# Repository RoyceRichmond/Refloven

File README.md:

# Refloven

this projects aims to be a low cost and customisable reflow oven board, i inspired this in the job made by @rocketscream reflow oven shield with some additional hardware so it can have more I/O pins avaliable and also usb so there's need of external programmer.

currently working to fix some problems, v2 is actually really stable and works fine. have fun and as a side note, use the v1 to make the v2 got it ? (like a 3d printer )

v1 is the easies one to build, all by hand and some extra wire.

v2 is a little more complicated to, but if you sucessfully assembled v1 and tested it you have everything on your side. it works either with 328p or 328pb only difference is how to program it and the mapping of the i/o

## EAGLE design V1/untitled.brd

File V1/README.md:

side note, you must change the i/o pins assigned to the 595 'cause a6 and a7 are just analog and not digital (why i dont undestand but meh) otherwise te lcd wont work

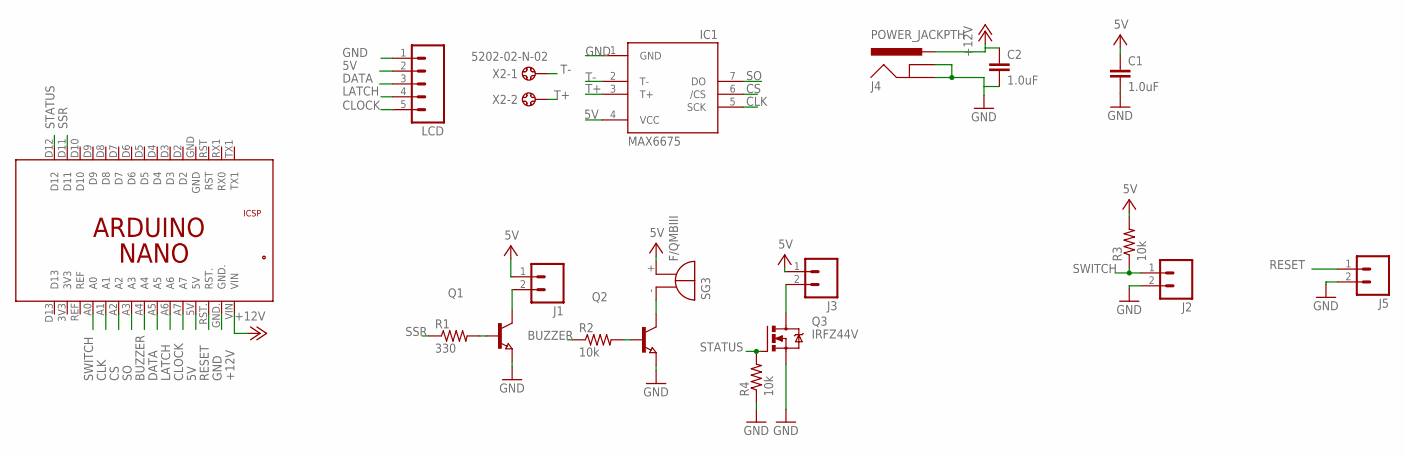
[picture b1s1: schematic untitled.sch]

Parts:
C1, C2: 1.0uF; 1206-CAP
IC1: MAX6675; SO08
J1, J2, J3, J5: M02PTH; 1X02
J4: POWER_JACKPTH; POWER_JACK_PTH
LCD: M05PTH; 1X05
PCB2: ARDUINO_NANO_RHEYD; ARDUINO_NANO
Q1, Q2: NPN-TRANSISTOR_SOT23; SOT23
Q3: IRFZ44V; TO220BH
R1: 330; R1206
R2, R3, R4: 10k; R1206
SG3: F/QMBIII
X2: 5202-02-N-02

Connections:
5V: C1.1, IC1.4 (VCC), J1.1, J3.1, LCD.2, PCB2.5V, R3.2, SG3.+ (-)
+12V: C2.1, J4.PWR, PCB2.VIN
BUZZER: PCB2.A4, R2.1
CLK: IC1.5 (SCK), PCB2.A1
CLOCK: LCD.5, PCB2.A7
CS: IC1.6 (/CS), PCB2.A2
DATA: LCD.3, PCB2.A5
GND: C1.2, C2.2, IC1.1 (GND), J2.2, J4.GND, J4.GNDBREAK, J5.2, LCD.1, PCB2.GND., Q1.2 (E), Q2.2 (E), Q3.S, R4.1
LATCH: LCD.4, PCB2.A6
unnamed: Q1.1 (B), R1.2
unnamed: Q2.1 (B), R2.2
unnamed: Q2.3 (C), SG3.- (+)
unnamed: J1.2, Q1.3 (C)
unnamed: J3.2, Q3.D
RESET: J5.1, PCB2.RST.
SO: IC1.7 (DO), PCB2.A3
SSR: PCB2.D11, R1.1
STATUS: PCB2.D12, Q3.G, R4.2
SWITCH: J2.1, PCB2.A0, R3.1
T+: IC1.3 (T+), X2.2
T-: IC1.2 (T-), X2.1

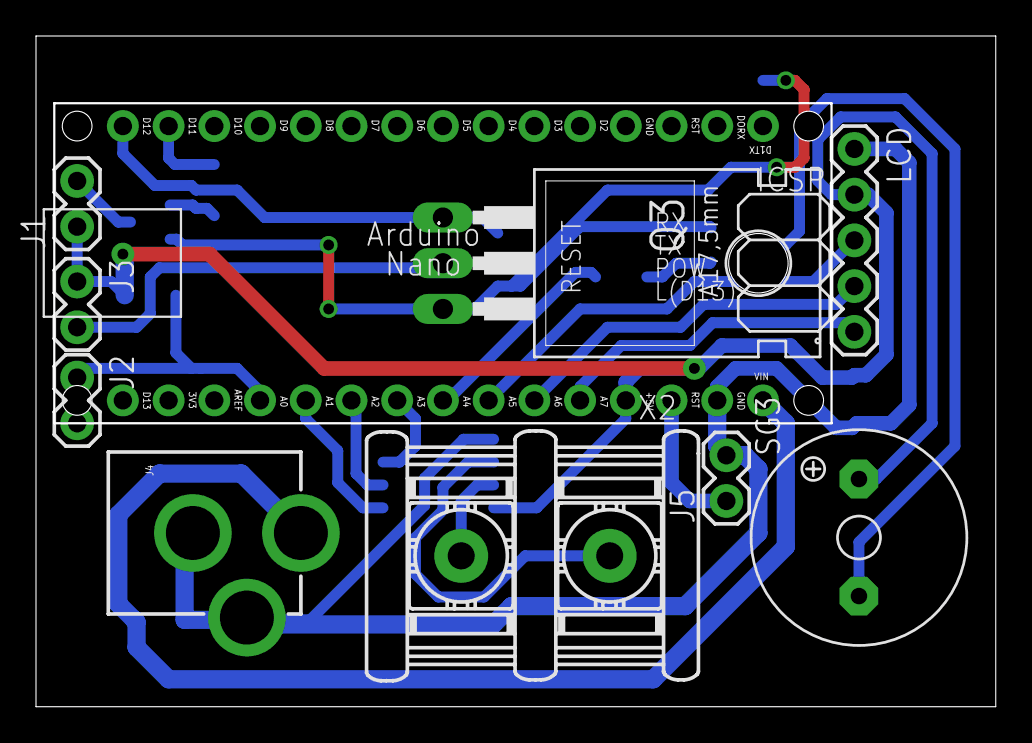
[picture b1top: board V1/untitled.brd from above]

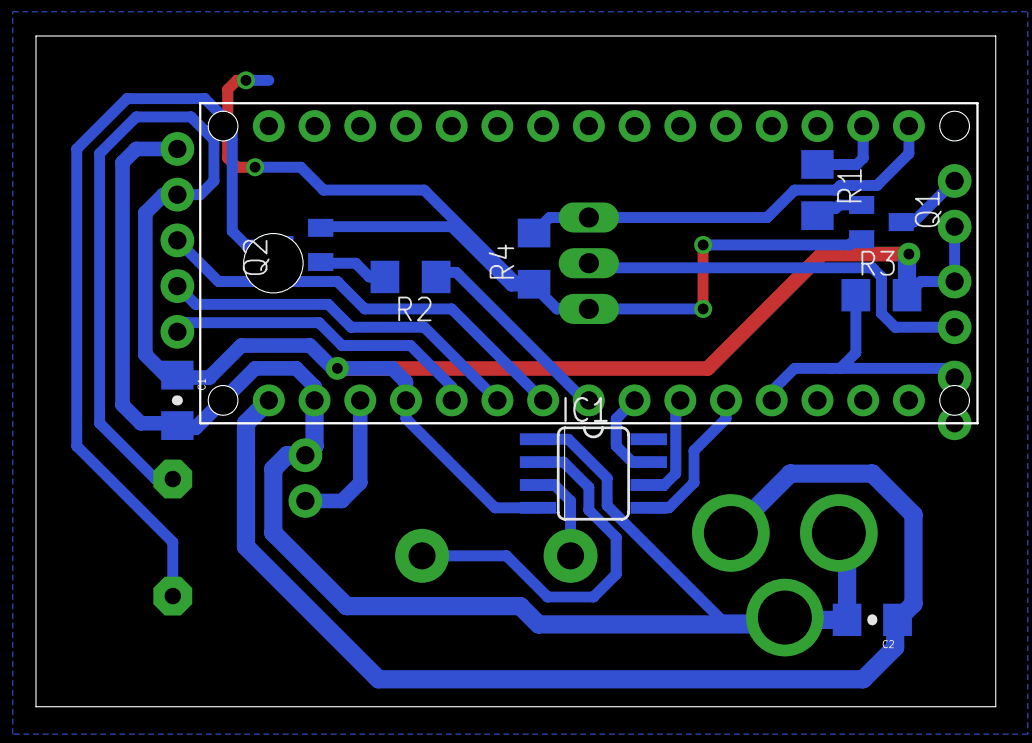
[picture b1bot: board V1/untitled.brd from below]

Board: 2 copper layers, 53.3 x 37.3 mm, 19 parts (9 on the bottom side), 21 nets.

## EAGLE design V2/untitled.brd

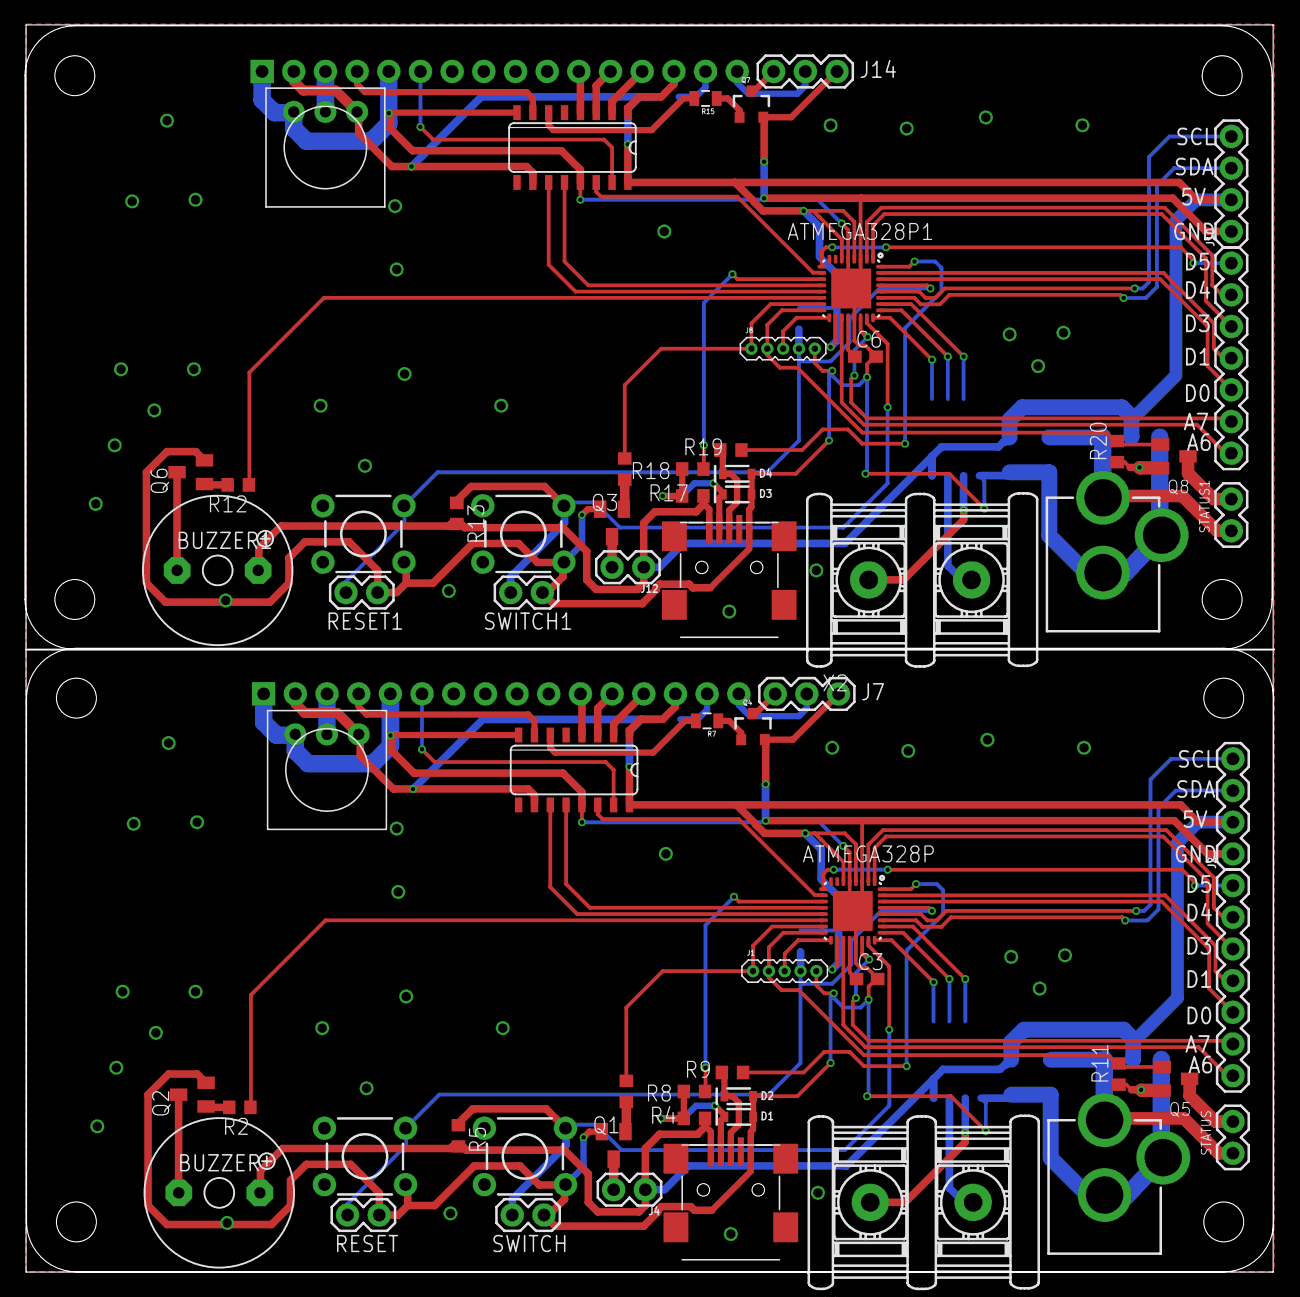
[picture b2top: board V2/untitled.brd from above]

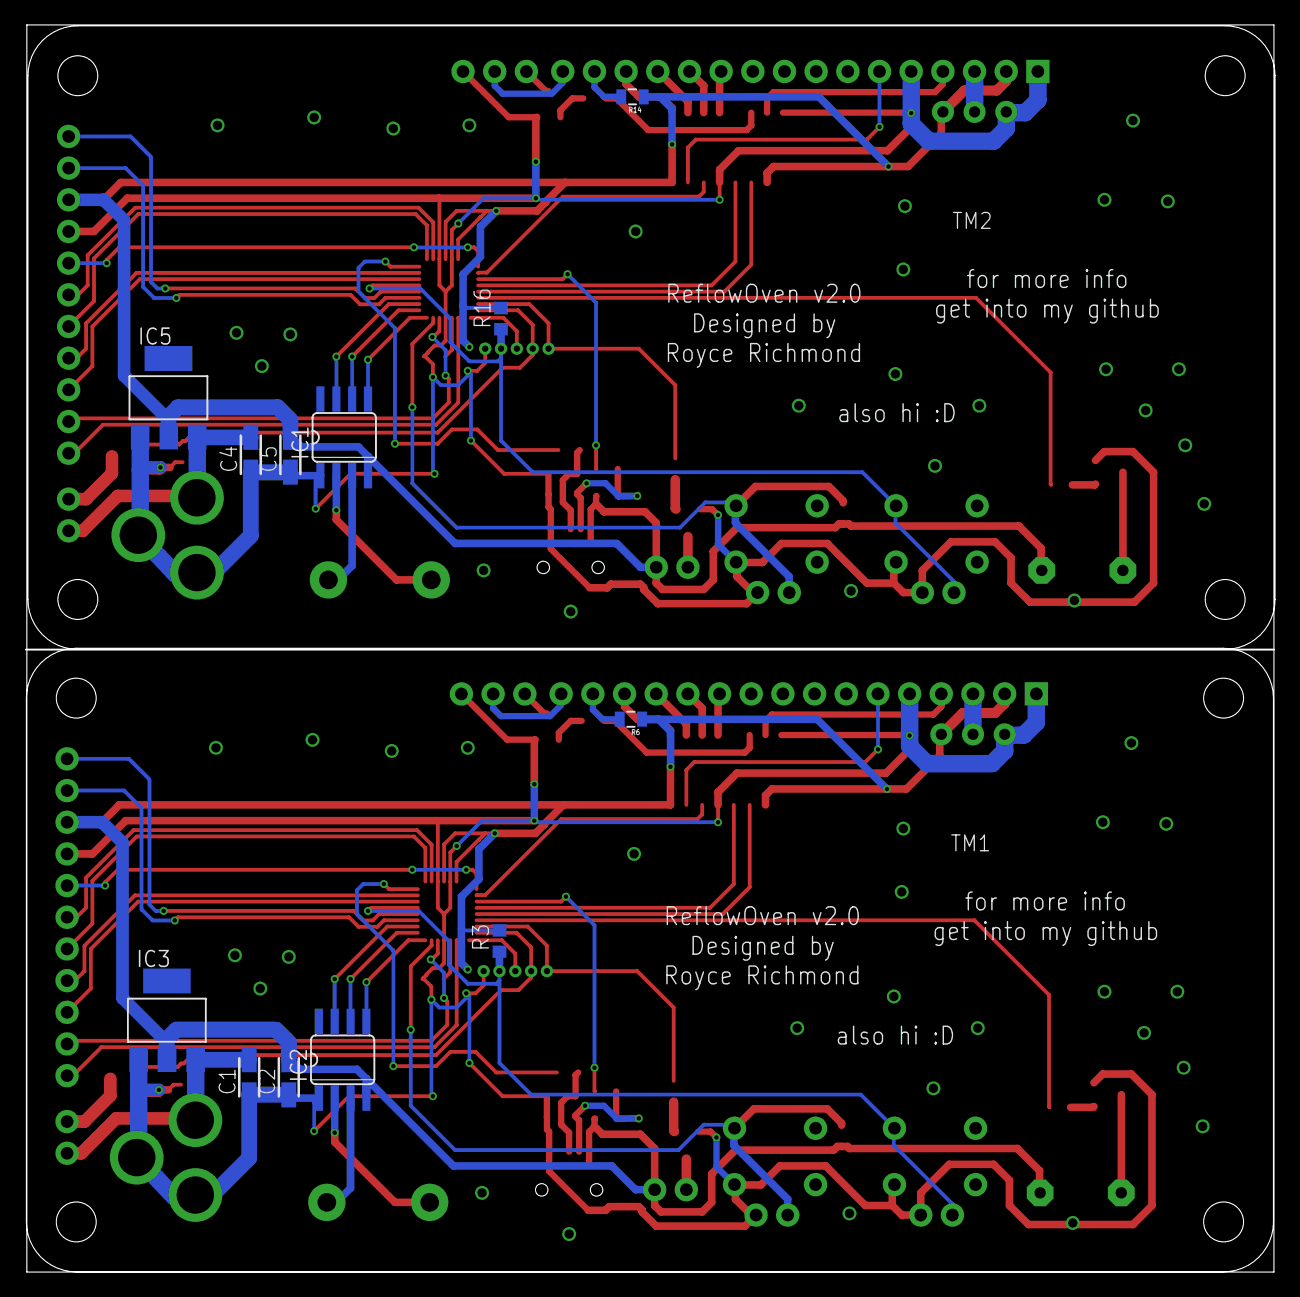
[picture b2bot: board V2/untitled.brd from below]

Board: 2 copper layers, 100.0 x 100.0 mm, 80 parts (12 on the bottom side), 95 nets.

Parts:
ATMEGA328P, ATMEGA328P1: MLF32-PAD
BUZZER, BUZZER1: F/QMBIII
C1, C2, C4, C5: 10uF; CT3216
C3, C6: C0603
CN1, CN2: USB-MINIB
D1, D2, D3, D4: 3.6V; SOD-323
IC1, IC2: MAX6675; SO08
IC3, IC5: REG1117; SOT223
IC4, IC6: 74LS595D; SO16
J1, J8: 1X05-1.27MM
J2, J10: 1X04
J3, J11: POWER_JACK; POWER_JACK_PTH
J4, J5, J6, J12, J13, J15: 1X02
J7, J14: 1X03
J9, J16: 1X07
PCB1, PCB2: PCB_DP_RECTANGLE-50X100; DP10050_V1
Q1, Q2, Q3, Q5, Q6, Q8: SOT23
Q4, Q7: MMBT2222A; SOT23-3
R1, R2, R10, R12: 330; R0603
R3, R5, R11, R13, R16, R20: 10k; R0603
R4, R17: 1.5K; R0603
R6, R14: 330; 0805
R7, R15: 1K; 0805
R8, R9, R18, R19: 68; R0603
RESET, RESET1: MOMENTARY-SWITCH-SPST-PTH-6.0MM; TACTILE_SWITCH_PTH_6.0MM
STATUS, STATUS1: 1X02
SWITCH, SWITCH1: MOMENTARY-SWITCH-SPST-PTH-6.0MM; TACTILE_SWITCH_PTH_6.0MM
TM1, TM2: TRIM-3386
U1, U3: LCD-16X2NOHOLES; LCD-16X2_NOHOLES
X1, X2: 5202-02-N-02

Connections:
+5V: ATMEGA328P.4, ATMEGA328P.6, ATMEGA328P.18, BUZZER.+, C2.+, CN1.VBUS, IC2.4, IC3.2, IC4.10, IC4.16, J2.2, J4.1, R3.2, R4.2, R5.2, R6.1, TM1.1, U3.2
+5V1: ATMEGA328P1.4, ATMEGA328P1.6, ATMEGA328P1.18, BUZZER1.+, C5.+, CN2.VBUS, IC1.4, IC5.2, IC6.10, IC6.16, J10.2, J12.1, R13.2, R14.1, R16.2, R17.2, TM2.1, U1.2
+12V: C1.+, IC3.3, J3.PWR, STATUS.1
+12V1: C4.+, IC5.3, J11.PWR, STATUS1.1
A1: ATMEGA328P1.19, J16.1
A2: ATMEGA328P1.22, J16.2
A6: ATMEGA328P.19, J9.1
A7: ATMEGA328P.22, J9.2
BUZZER: ATMEGA328P.14, R2.1
BUZZER1: ATMEGA328P1.14, R12.1
CLK: ATMEGA328P.24, IC2.5
CLK1: ATMEGA328P1.24, IC1.5
CLOCK: ATMEGA328P.13, IC4.11
CLOCK1: ATMEGA328P1.13, IC6.11
CS: ATMEGA328P.25, IC2.6
CS1: ATMEGA328P1.25, IC1.6
D1: ATMEGA328P1.17, J8.3
D2: ATMEGA328P.32, R9.1
D3: ATMEGA328P.1, J9.5
D4: ATMEGA328P.2, J9.6
D5: ATMEGA328P.9, J9.7
D6: ATMEGA328P1.11, R18.1
D7: ATMEGA328P.11, R8.1
D8: ATMEGA328P1.9, J16.7
D9: ATMEGA328P1.2, J16.6
D10: ATMEGA328P1.1, J16.5
D11: ATMEGA328P1.32, R19.1
D13: ATMEGA328P.17, J1.3
DATA: ATMEGA328P.10, IC4.14
DATA1: ATMEGA328P1.10, IC6.14
GND: ATMEGA328P.3, ATMEGA328P.5, ATMEGA328P.21, ATMEGA328P.PAD, ATMEGA328P1.3, ATMEGA328P1.5, ATMEGA328P1.21, ATMEGA328P1.PAD, C1.-, C2.-, C3.2, C4.-, C5.-, C6.2, CN1.GND, CN2.GND, D1.A, D2.A, D3.A, D4.A, IC1.1, IC2.1, IC3.1, IC4.8, IC4.13, IC5.1, IC6.8, IC6.13, J1.5, J2.1, J3.GND, J3.GNDBREAK, J5.2, J6.2, J7.1, J8.5, J10.1, J11.GND, J11.GNDBREAK, J13.2, J14.1, J15.2, Q1.2, Q2.2, Q3.2, Q4.2, Q5.2, Q6.2, Q7.2, Q8.2, R11.1, R20.1, RESET.1, RESET1.1, SWITCH.1, SWITCH1.1, TM1.3, TM2.3, U1.1, U1.5, U3.1, U3.5
LATCH: ATMEGA328P.12, IC4.12
LATCH1: ATMEGA328P1.12, IC6.12
unnamed: BUZZER.-, Q2.3
unnamed: IC2.2, X1.1
unnamed: IC2.3, X1.2
unnamed: Q1.1, R1.2
unnamed: Q2.1, R2.2
unnamed: ATMEGA328P.20, C3.1
unnamed: J4.2, Q1.3
unnamed: R6.2, U3.15
unnamed: TM1.2, U3.3
unnamed: IC4.7, U3.4
unnamed: IC4.15, U3.6
unnamed: IC4.4, U3.11
unnamed: IC4.3, U3.12
unnamed: IC4.2, U3.13
unnamed: IC4.1, U3.14
unnamed: J7.2, U3.16
unnamed: J7.3, Q4.3
unnamed: Q4.1, R7.1
unnamed: IC4.6, R7.2
unnamed: CN1.D-, D1.C, R4.1, R8.2
unnamed: CN1.D+, D2.C, R9.2
unnamed: BUZZER1.-, Q6.3
unnamed: IC1.2, X2.1
unnamed: Q5.3, STATUS.2
unnamed: IC1.3, X2.2
unnamed: Q3.1, R10.2
unnamed: Q6.1, R12.2
unnamed: J12.2, Q3.3
unnamed: R14.2, U1.15
unnamed: TM2.2, U1.3
unnamed: IC6.7, U1.4
unnamed: IC6.15, U1.6
unnamed: IC6.4, U1.11
unnamed: IC6.3, U1.12
unnamed: IC6.2, U1.13
unnamed: IC6.1, U1.14
unnamed: J14.2, U1.16
unnamed: J14.3, Q7.3
unnamed: Q7.1, R15.1
unnamed: IC6.6, R15.2
unnamed: ATMEGA328P1.20, C6.1
unnamed: CN2.D-, D3.C, R17.1, R18.2
unnamed: CN2.D+, D4.C, R19.2
unnamed: Q8.3, STATUS1.2
RESET: ATMEGA328P.29, J1.4, J5.1, R3.1, RESET.3
RESET1: ATMEGA328P1.29, J8.4, J15.1, R16.1, RESET1.3
RXD: ATMEGA328P.30, J9.3
RXD1: ATMEGA328P1.30, J16.3
SCL: ATMEGA328P.28, J2.4
SCL1: ATMEGA328P1.28, J10.4
SDA: ATMEGA328P.27, J2.3
SDA1: ATMEGA328P1.27, J10.3
SO: ATMEGA328P.26, IC2.7
SO1: ATMEGA328P1.26, IC1.7
SSR: ATMEGA328P.15, J1.1, R1.1
SSR1: ATMEGA328P1.15, J8.1, R10.1
STATUS: ATMEGA328P.16, J1.2, Q5.1, R11.2
STATUS1: ATMEGA328P1.16, J8.2, Q8.1, R20.2
SWITCH: ATMEGA328P.23, J6.1, R5.1, SWITCH.3
SWITCH1: ATMEGA328P1.23, J13.1, R13.1, SWITCH1.3
TXD: ATMEGA328P.31, J9.4
TXD1: ATMEGA328P1.31, J16.4

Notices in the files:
parts and their libraries:
SparkFun-Connectors: Licensing: Creative Commons ShareAlike 4.0 International - https://creativecommons.org/licenses/by-sa/4.0
